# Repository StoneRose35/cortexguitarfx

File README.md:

# Introduction
The PiPicoFX is a simple multieffects unit for Guitar built around a Raspberry Pi Pico board. It is capable of serving as a standalone Amp-Simulator in conjuctions with a general-purpose PA system. 
## Audio Engine Specs
* 48 kHz sampling rate
* 0.6 ms Latency
* 16 bit fixed point accuracy
* Mono Input and output
## Controls
* 3 Parameters directly accessible via Knobs
* 128*64 Pixel monochrome display
* 1 Encoder, 2 Pushbuttons
* Analog Volume Control 
# Building
## Material needed
* Raspberry Pi Pico Board
* Audio Codec Board
* 128*64 Pixel OLED Display, compatible with SSD1306 driver
* Rotary Encoder (full quadrature)
* 5 10k Potentiometer
* 2 Pushbuttons
* 2 6.3 Mono Jacks 
* Enclosure
* Power Connector
## Audio-Codec Board
Generally an audio codec able to operate in 48 kHz I2S Master Mode is able to work with the raspberry pi pico. In fact at the beginning of the development even the internal ADC of the Pi Pico served as an input. The most straightforward and probably best-sounding way is to build the audio-codec pcb's using the [gerberfiles](schematics/guitarpreamp/audiocodecboard.zip) from your favorite small-batch manufacturer and then using the [bom](schematics/guitarpreamp/audiocodecboard_bom.csv) to order the parts from your preferred electronics distributor. Of course some SMD-soldering is required as well... 
### Schematic

## Software Installation
Download [pipicofx.uf2](pipicofx.uf2). Then connect the Raspberry Pi Pico while having the "boot" button depressed. Drag the file downloaded to the mass-storage device showing up, then you are done.

 ## Assembly
 Mount the UI Elements (Buttons, Encoder, Potentiometers, Jacks, Power connector) to the Enclosure the wire up the entire system using the sketch shown below

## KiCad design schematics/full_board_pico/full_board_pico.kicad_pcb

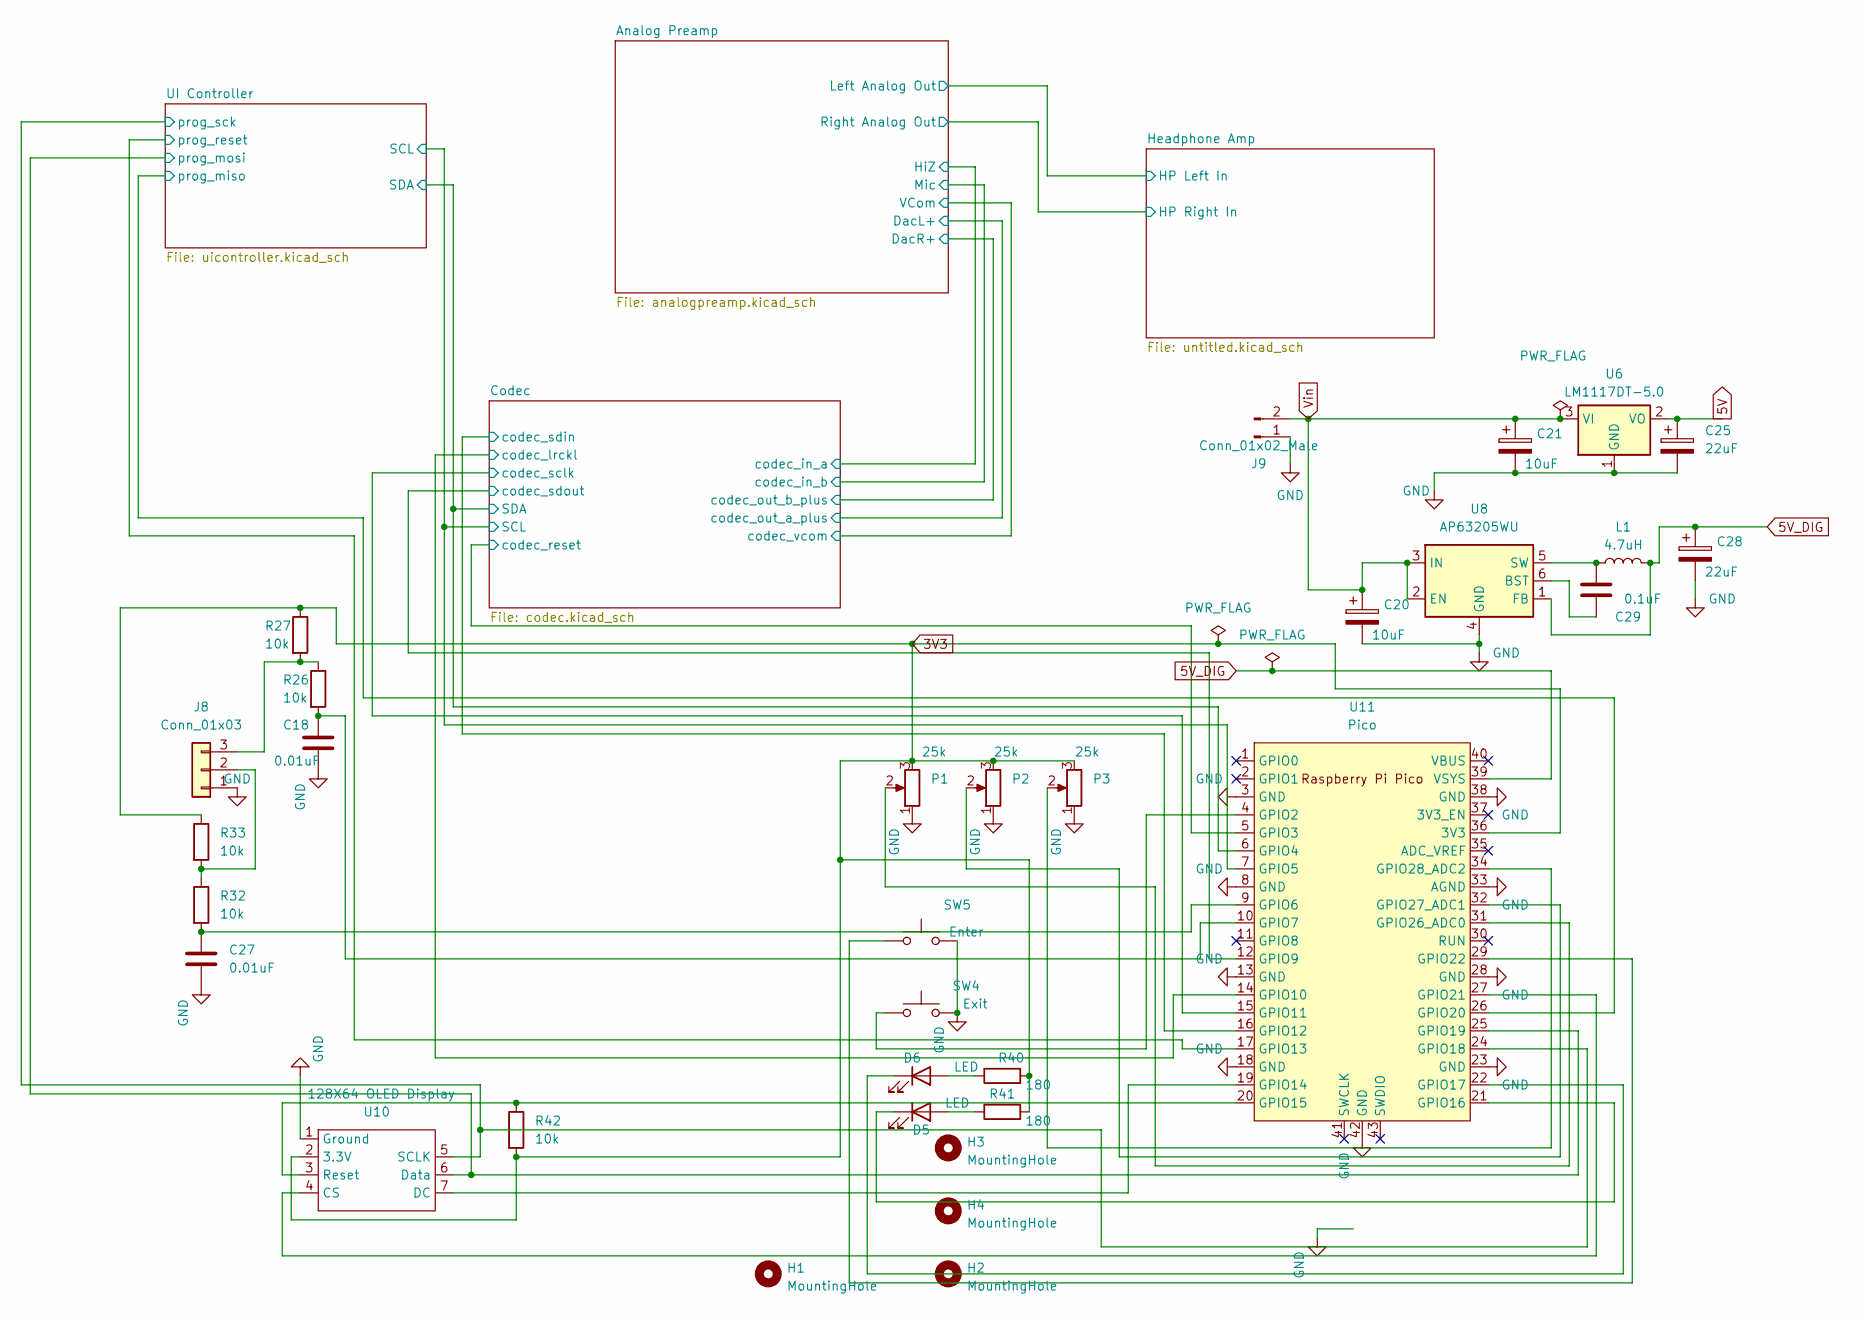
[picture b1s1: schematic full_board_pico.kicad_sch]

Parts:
C18, C27: 0.01uF; C_0805_2012Metric_Pad1.18x1.45mm_HandSolder
C20, C21: 10uF; CP_Elec_4x4.5
C25, C28: 22uF; CP_Elec_4x4.5
C29: 0.1uF; C_0805_2012Metric_Pad1.18x1.45mm_HandSolder
D5, D6: LED; PinHeader_1x02_P2.54mm_Vertical
H1, H2, H3, H4: MountingHole; MountingHole_4.3mm_M4
J8: Conn_01x03; PinHeader_1x03_P2.54mm_Vertical
J9: Conn_01x02_Male; PinHeader_1x02_P2.54mm_Vertical
L1: 4.7uH; L_Bourns_SRP7028A_7.3x6.6mm
P1, P2, P3: 25k; PinHeader_1x03_P2.54mm_Vertical
R26, R27, R32, R33, R42: 10k; R_0603_1608Metric_Pad0.98x0.95mm_HandSolder
R40, R41: 180; R_0603_1608Metric_Pad0.98x0.95mm_HandSolder
SW4: Exit; PinHeader_1x02_P2.54mm_Vertical
SW5: Enter; PinHeader_1x02_P2.54mm_Vertical
U6: LM1117DT-5.0; TO-252-2
U8: AP63205WU; TSOT-23-6
U10: 128X64 OLED Display; PinHeader_1x07_P2.54mm_Vertical
U11: Pico; RPi_Pico_SMD_TH

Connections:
5V_DIG: C28.1, L1.2, U8.1 (FB), U11.39 (VSYS)
/Codec/codec_lrckl: U11.14 (GPIO10); also elsewhere on the board
/Codec/codec_reset: U11.5 (GPIO3); also elsewhere on the board
/Codec/codec_sclk: U11.15 (GPIO11); also elsewhere on the board
/Codec/codec_sdin: U11.16 (GPIO12); also elsewhere on the board
/Codec/codec_sdout: U11.12 (GPIO9); also elsewhere on the board
/UI Controller/prog_miso: U11.26 (GPIO20); also elsewhere on the board
/UI Controller/prog_mosi: U10.6 (Data), U11.25 (GPIO19); also elsewhere on the board
/UI Controller/prog_reset: U11.17 (GPIO13); also elsewhere on the board
/UI Controller/prog_sck: U10.5 (SCLK), U11.24 (GPIO18); also elsewhere on the board
unnamed: D5.2 (A), R41.1
unnamed: D5.1 (K), U11.21 (GPIO16)
unnamed: D6.2 (A), R40.1
unnamed: D6.1 (K), U11.22 (GPIO17)
unnamed: J8.2, R32.1, R33.2
unnamed: J8.3, R26.1, R27.2
unnamed: C29.1, U8.6 (BST)
unnamed: C29.2, L1.1, U8.5 (SW)
unnamed: U10.4 (CS), U11.27 (GPIO21)
unnamed: U10.7 (DC), U11.19 (GPIO14)
unnamed: R42.1, U10.3 (Reset), U11.20 (GPIO15)
unnamed: SW4.1, U11.4 (GPIO2)
unnamed: C27.1, R32.2, U11.9 (GPIO6)
unnamed: C18.1, R26.2, U11.10 (GPIO7)
unnamed: SW5.1, U11.29 (GPIO22)
unnamed: P1.2, U11.31 (GPIO26_ADC0)
unnamed: P2.2, U11.32 (GPIO27_ADC1)
unnamed: P3.2, U11.34 (GPIO28_ADC2)
Vin: C20.1, C21.1, J9.2, U6.3 (VI), U8.2 (EN), U8.3 (IN)

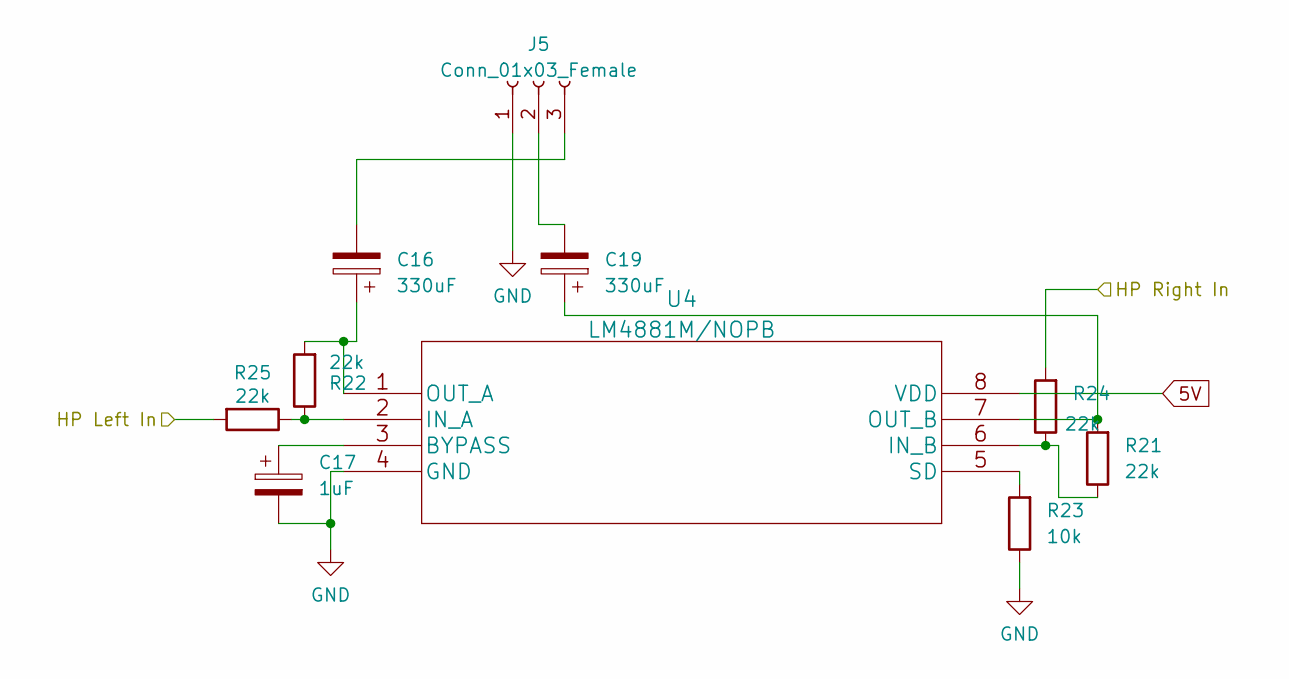
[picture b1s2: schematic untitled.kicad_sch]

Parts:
C16, C19: 330uF; CP_Elec_6.3x7.7
C17: 1uF; CP_Elec_4x4.5
J5: Conn_01x03_Female; PinHeader_1x03_P2.54mm_Vertical
R21, R22, R24, R25: 22k; R_0603_1608Metric_Pad0.98x0.95mm_HandSolder
R23: 10k; R_0603_1608Metric_Pad0.98x0.95mm_HandSolder
U4: LM4881M/NOPB; SOIC-8_3.9x4.9mm_P1.27mm

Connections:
unnamed: C19.2, J5.2
unnamed: C16.2, J5.3
unnamed: C17.1, U4.3 (BYPASS)
unnamed: R22.1, R25.1, U4.2 (IN_A)
unnamed: R21.1, R24.1, U4.6 (IN_B)
unnamed: C16.1, R22.2, U4.1 (OUT_A)
unnamed: C19.1, R21.2, U4.7 (OUT_B)
unnamed: R23.2, U4.5 (SD)

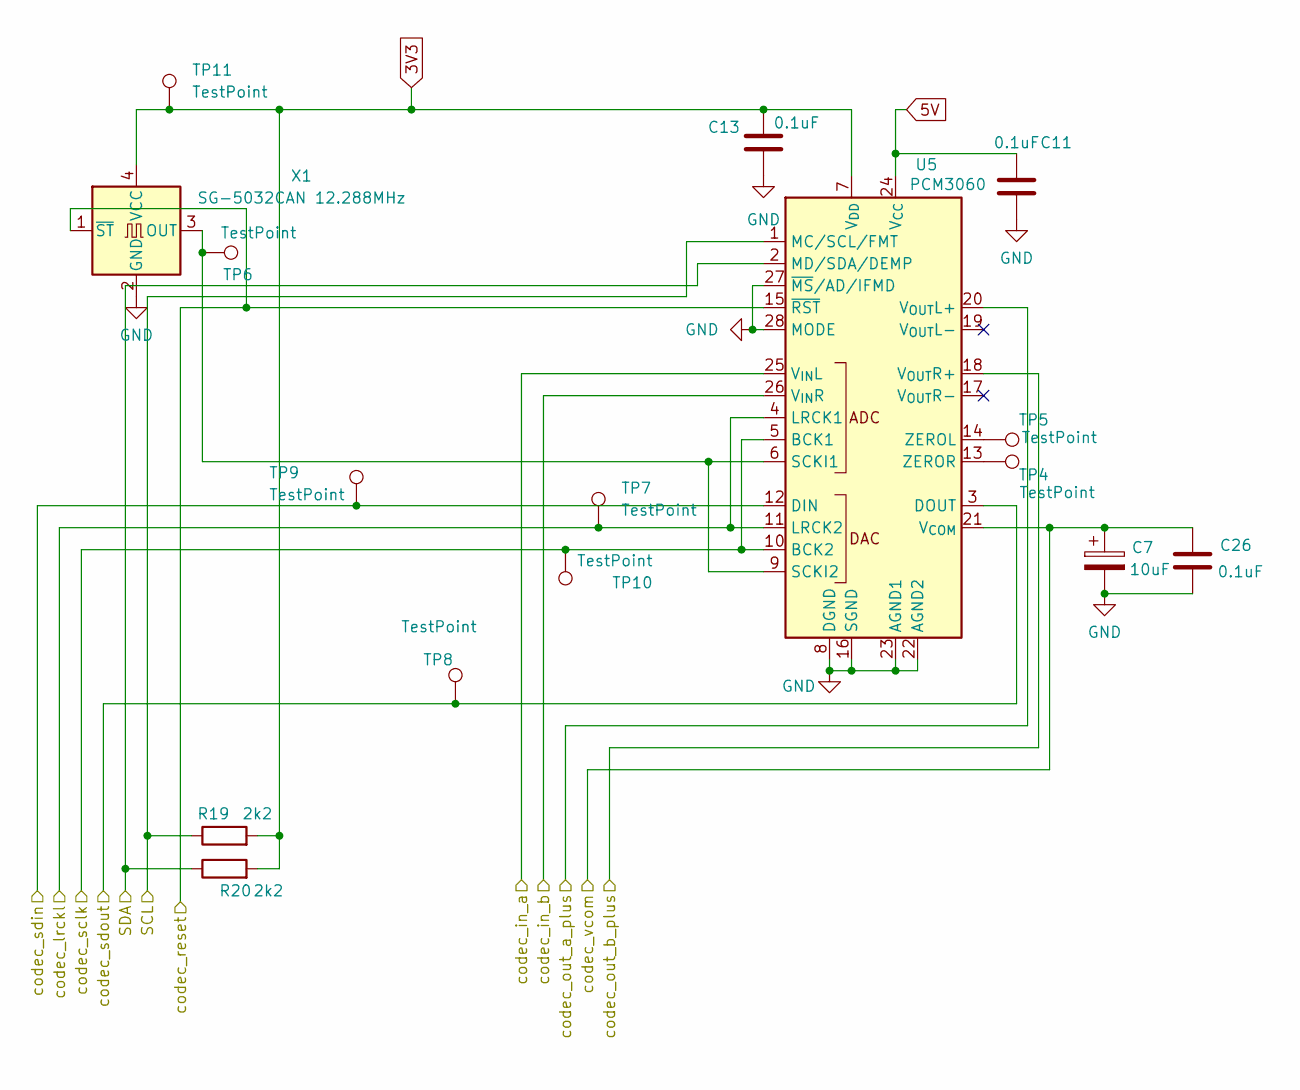
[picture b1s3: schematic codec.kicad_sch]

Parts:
C7: 10uF; CP_Elec_4x4.5
C11, C13, C26: 0.1uF; C_0805_2012Metric_Pad1.18x1.45mm_HandSolder
R19, R20: 2k2; R_0603_1608Metric_Pad0.98x0.95mm_HandSolder
TP4, TP5, TP6, TP7, TP8, TP9, TP10, TP11: TestPoint; TestPoint_Pad_D1.5mm
U5: PCM3060; TSSOP-28_4.4x9.7mm_P0.65mm
X1: SG-5032CAN 12.288MHz; Oscillator_SMD_SeikoEpson_SG8002CA-4Pin_7.0x5.0mm_HandSolde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

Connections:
/Analog Preamp/DacL+: U5.20 (V_{OUT}L+); also elsewhere on the board
/Analog Preamp/DacR+: U5.18 (V_{OUT}R+); also elsewhere on the board
/Analog Preamp/HiZ: U5.25 (V_{IN}L); also elsewhere on the board
/Analog Preamp/Mic: U5.26 (V_{IN}R); also elsewhere on the board
/Analog Preamp/VCom: C7.1, C26.1, U5.21 (V_{COM}); also elsewhere on the board
/Codec/codec_lrckl: TP7.1, U5.4 (LRCK1), U5.11 (LRCK2); also elsewhere on the board
/Codec/codec_reset: U5.15 (~RST), X1.1 (~ST); also elsewhere on the board
/Codec/codec_sclk: TP10.1, U5.5 (BCK1), U5.10 (BCK2); also elsewhere on the board
/Codec/codec_sdin: TP9.1, U5.12 (DIN); also elsewhere on the board
/Codec/codec_sdout: TP8.1, U5.3 (DOUT); also elsewhere on the board
unnamed: TP6.1, U5.6 (SCKI1), U5.9 (SCKI2), X1.3 (OUT)
unnamed: TP5.1, U5.14 (ZEROL)
unnamed: TP4.1, U5.13 (ZEROR)

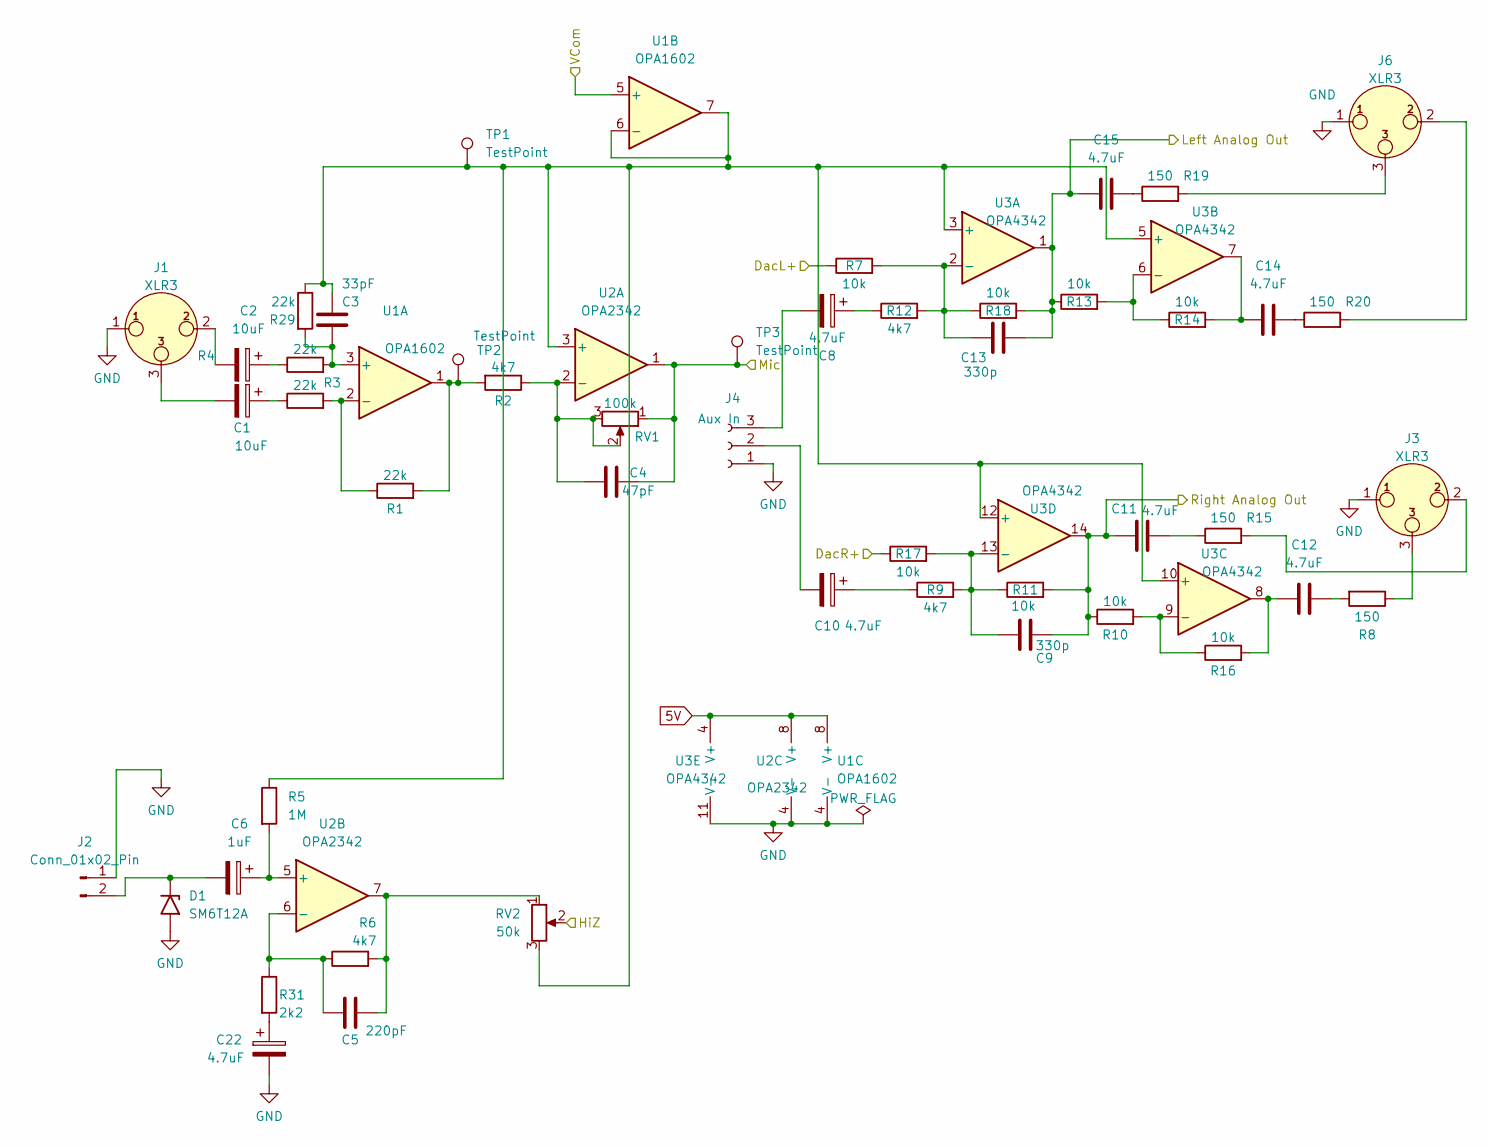
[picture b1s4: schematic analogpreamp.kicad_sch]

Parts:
C1, C2: 10uF; CP_Elec_4x4.5
C3: 33pF; C_0805_2012Metric_Pad1.18x1.45mm_HandSolder
C4: 47pF; C_0603_1608Metric_Pad1.08x0.95mm_HandSolder
C5: 220pF; C_0603_1608Metric_Pad1.08x0.95mm_HandSolder
C6: 1uF; CP_Elec_4x4.5
C8, C10, C22: 4.7uF; CP_Elec_4x4.5
C9, C13: 330p; C_0603_1608Metric_Pad1.08x0.95mm_HandSolder
C11, C12, C14, C15: 4.7uF; CP_Elec_5x5.4
D1: SM6T12A; D_SMB
J1, J3, J6: XLR3; PinHeader_1x03_P2.54mm_Vertical
J2: Conn_01x02_Pin; PinHeader_1x02_P2.54mm_Vertical
J4: Aux In; PinHeader_1x03_P2.54mm_Vertical
R1, R3, R4, R29: 22k; R_0603_1608Metric_Pad0.98x0.95mm_HandSolder
R2, R6, R9, R12: 4k7; R_0603_1608Metric_Pad0.98x0.95mm_HandSolder
R5: 1M; R_0603_1608Metric_Pad0.98x0.95mm_HandSolder
R7, R10, R11, R13, R14, R16, R17, R18: 10k; R_0603_1608Metric_Pad0.98x0.95mm_HandSolder
R8, R15, R19, R20: 150; R_0603_1608Metric_Pad0.98x0.95mm_HandSolder
R31: 2k2; R_0603_1608Metric_Pad0.98x0.95mm_HandSolder
RV1: 100k; PinHeader_1x03_P2.54mm_Vertical
RV2: 50k; PinHeader_1x03_P2.54mm_Vertical
TP1, TP2, TP3: TestPoint; TestPoint_Pad_D1.5mm
U1: OPA1602; SOIC-8_3.9x4.9mm_P1.27mm
U2: OPA2342; SOIC-8_3.9x4.9mm_P1.27mm
U3: OPA4342; SOIC-14_3.9x8.7mm_P1.27mm

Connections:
/Analog Preamp/DacL+: R7.1; also elsewhere on the board
/Analog Preamp/DacR+: R17.1; also elsewhere on the board
/Analog Preamp/HiZ: RV2.2; also elsewhere on the board
/Analog Preamp/Mic: C4.2, RV1.1, TP3.1, U2.1; also elsewhere on the board
/Analog Preamp/VCom: U1.5 (+); also elsewhere on the board
unnamed: C1.1, R3.1
unnamed: C1.2, J1.3
unnamed: C2.1, R4.1
unnamed: C2.2, J1.2
unnamed: C5.2, R6.2, RV2.1, U2.7
unnamed: C8.1, R12.1
unnamed: C10.1, R9.1
unnamed: C12.1, R16.2, U3.8
unnamed: C12.2, R8.2
unnamed: C14.1, R14.2, U3.7
unnamed: C22.1, R31.2
unnamed: C6.2, D1.1 (A1), J2.2
unnamed: J3.2, R15.2
unnamed: J3.3, R8.1
unnamed: C10.2, J4.2
unnamed: C8.2, J4.3
unnamed: R1.2, R2.2, TP2.1, U1.1
unnamed: C3.2, R4.2, R29.2, U1.3 (+)
unnamed: R1.1, R3.2, U1.2 (-)
unnamed: C3.1, R5.1, R29.1, RV2.3, TP1.1, U1.6 (-), U1.7, U2.3 (+), U3.3 (+), U3.5 (+), U3.10 (+), U3.12 (+)
unnamed: C4.1, R2.1, RV1.2, RV1.3, U2.2 (-)
unnamed: C6.1, R5.2, U2.5 (+)
unnamed: C5.1, R6.1, R31.1, U2.6 (-)
unnamed: R13.2, R14.1, U3.6 (-)
unnamed: R10.2, R16.1, U3.9 (-)
unnamed: C9.1, R9.2, R11.1, R17.2, U3.13 (-)

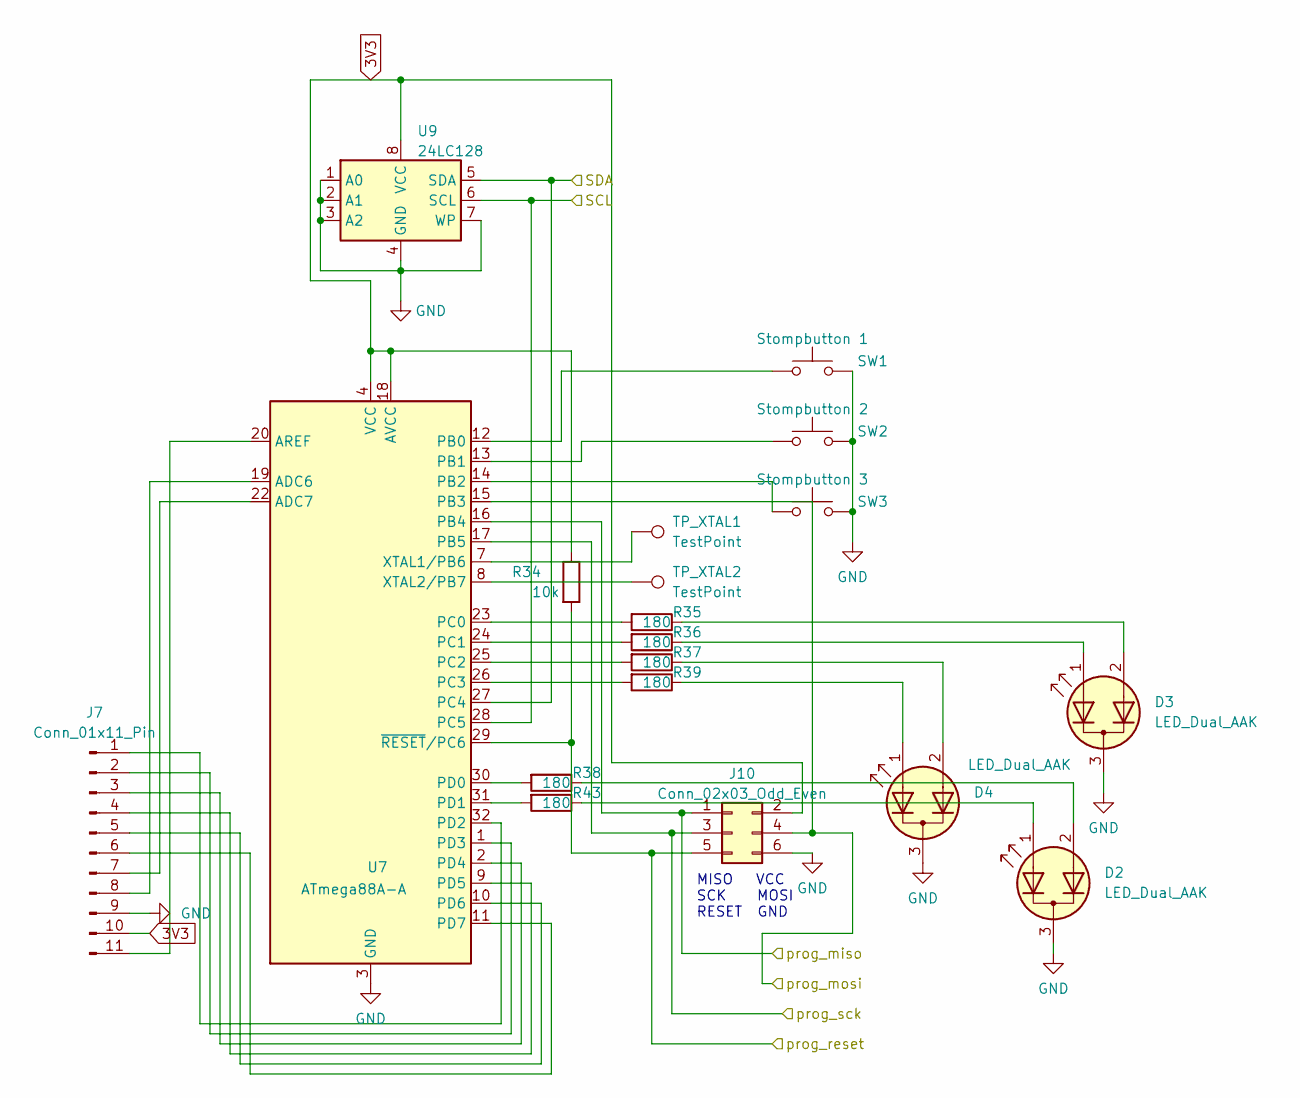
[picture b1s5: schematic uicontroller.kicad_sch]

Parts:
D2, D3, D4: LED_Dual_AAK; LED_D5.0mm-3
J7: Conn_01x11_Pin; PinHeader_1x11_P2.54mm_Vertical
J10: Conn_02x03_Odd_Even; PinHeader_2x03_P2.54mm_Vertical
R34: 10k; R_0603_1608Metric_Pad0.98x0.95mm_HandSolder
R35, R36, R37, R38, R39, R43: 180; R_0603_1608Metric_Pad0.98x0.95mm_HandSolder
SW1: Stompbutton 1; PinHeader_1x02_P2.54mm_Vertical
SW2: Stompbutton 2; PinHeader_1x02_P2.54mm_Vertical
SW3: Stompbutton 3; PinHeader_1x02_P2.54mm_Vertical
TP_XTAL1, TP_XTAL2: TestPoint; TestPoint_Pad_D1.5mm
U7: ATmega88A-A; TQFP-32_7x7mm_P0.8mm
U9: 24LC128; SOIC-8_3.9x4.9mm_P1.27mm

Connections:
/UI Controller/prog_miso: J10.1, U7.16 (PB4); also elsewhere on the board
/UI Controller/prog_mosi: J10.4, U7.15 (PB3); also elsewhere on the board
/UI Controller/prog_reset: J10.5, R34.2, U7.29 (~RESET/PC6); also elsewhere on the board
/UI Controller/prog_sck: J10.3, U7.17 (PB5); also elsewhere on the board
unnamed: D2.1 (A1), R43.1
unnamed: D2.2 (A2), R38.1
unnamed: D3.1 (A1), R36.1
unnamed: D3.2 (A2), R35.1
unnamed: D4.1 (A1), R39.1
unnamed: D4.2 (A2), R37.1
unnamed: J7.1, U7.32 (PD2)
unnamed: J7.2, U7.1 (PD3)
unnamed: J7.3, U7.2 (PD4)
unnamed: J7.4, U7.9 (PD5)
unnamed: J7.5, U7.10 (PD6)
unnamed: J7.6, U7.11 (PD7)
unnamed: J7.7, U7.22 (ADC7)
unnamed: J7.8, U7.19 (ADC6)
unnamed: J7.11, U7.20 (AREF)
unnamed: SW1.1, U7.12 (PB0)
unnamed: SW2.1, U7.13 (PB1)
unnamed: SW3.1, U7.14 (PB2)
unnamed: R35.2, U7.23 (PC0)
unnamed: R36.2, U7.24 (PC1)
unnamed: R37.2, U7.25 (PC2)
unnamed: R39.2, U7.26 (PC3)
unnamed: R38.2, U7.30 (PD0)
unnamed: R43.2, U7.31 (PD1)
unnamed: TP_XTAL1.1, U7.7 (XTAL1/PB6)
unnamed: TP_XTAL2.1, U7.8 (XTAL2/PB7)

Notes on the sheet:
MISO VCC SCK MOSI RESET GND

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
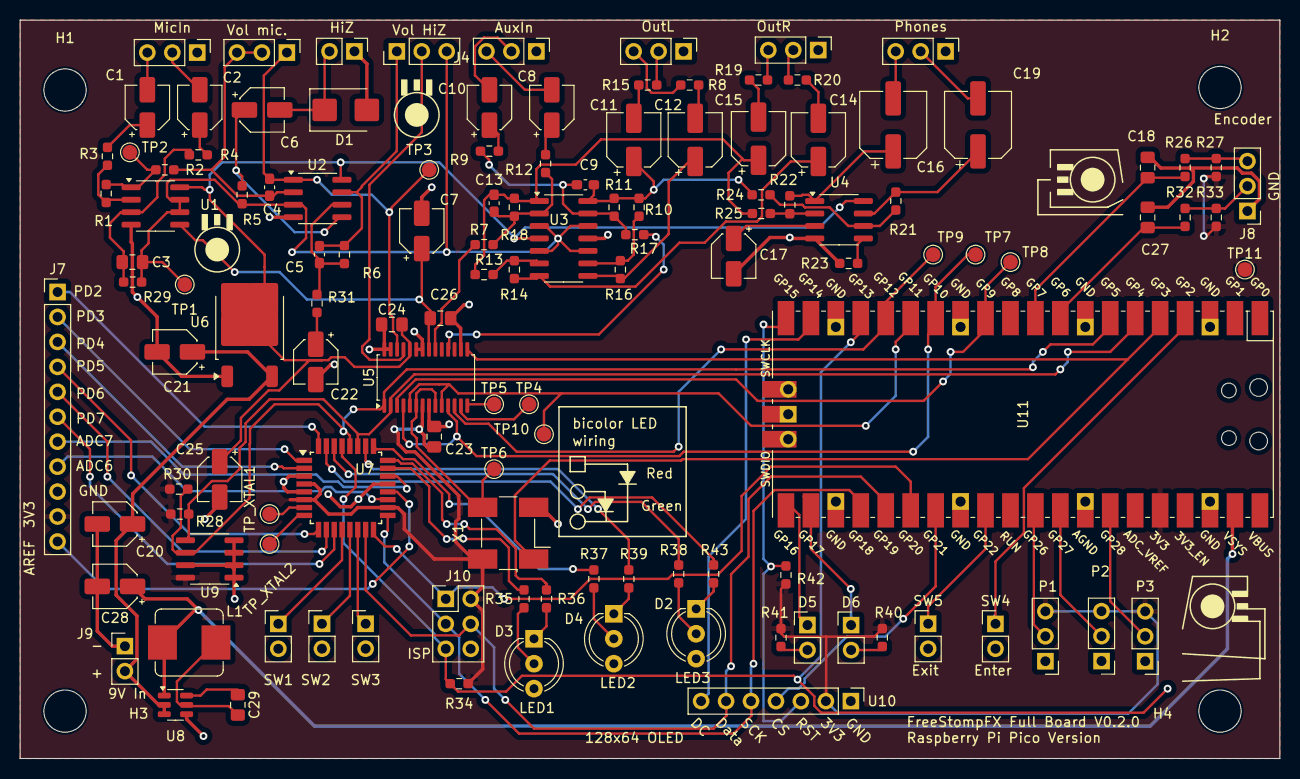
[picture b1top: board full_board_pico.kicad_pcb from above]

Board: 4 copper layers, 128.3 x 75.2 mm, 128 parts (0 on the bottom side), 110 nets.

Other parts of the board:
C23, C24: 0.1uF; C_0805_2012Metric_Pad1.18x1.45mm_HandSolder
R28, R30: 2k2; R_0603_1608Metric_Pad0.98x0.95mm_HandSolder

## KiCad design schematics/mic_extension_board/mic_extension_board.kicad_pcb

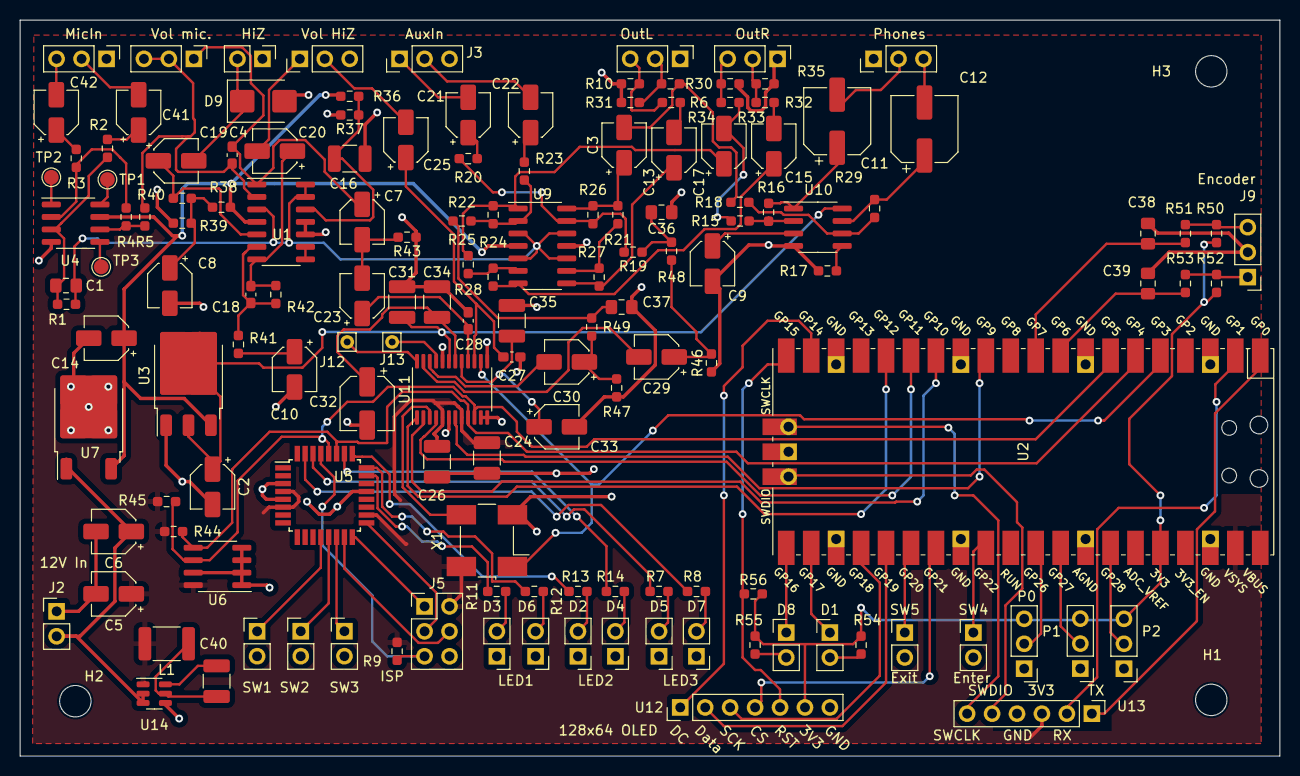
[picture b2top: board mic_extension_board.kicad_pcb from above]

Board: 4 copper layers, 128.3 x 74.9 mm, 149 parts (0 on the bottom side), 121 nets.

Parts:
C1: 33pF; C_0805_2012Metric_Pad1.18x1.45mm_HandSolder
C2, C7, C8, C9, C19, C20: 1uF; CP_Elec_4x4.5
C3, C6, C13, C15, C17, C23, C25, C33, C41, C42: 10uF; CP_Elec_4x4.5
C4: 47pF; C_0603_1608Metric_Pad1.08x0.95mm_HandSolder
C5, C14: 22uF; CP_Elec_4x4.5
C10, C21, C22: 4.7uF; CP_Elec_4x4.5
C11, C12: 330uF; CP_Elec_6.3x7.7
C16, C24, C26, C31, C34, C35, C40: 0.1uF; C_1210_3225Metric_Pad1.33x2.70mm_HandSolder
C18, C27, C28: 220pF; C_0603_1608Metric_Pad1.08x0.95mm_HandSolder
C29, C30: 3.3uF; CP_Elec_4x4.5
C32: 47uF; CP_Elec_5x5.4
C36, C37: 3.3nF; C_0805_2012Metric_Pad1.18x1.45mm_HandSolder
C38, C39: 0.01uF; C_0805_2012Metric_Pad1.18x1.45mm_HandSolder
D1, D2, D3, D4, D5, D6, D7, D8: LED; PinHeader_1x02_P2.54mm_Vertical
D9: SM6T12A; D_SMB
H1, H2, H3: MountingHole; MountingHole_3.2mm_M3
J1, J7, J8: XLR3; PinHeader_1x03_P2.54mm_Vertical
J2: Conn_01x02_Male; PinHeader_1x02_P2.54mm_Vertical
J3: Aux In; PinHeader_1x03_P2.54mm_Vertical
J4: Conn_01x02_Pin; PinHeader_1x02_P2.54mm_Vertical
J5: Conn_02x03_Odd_Even; PinHeader_2x03_P2.54mm_Vertical
J6: Conn_01x03_Female; PinHeader_1x03_P2.54mm_Vertical
J9: Conn_01x03; PinHeader_1x03_P2.54mm_Vertical
J12, J13: Conn_01x01_Female; Pin_D0.7mm_L6.5mm_W1.8mm_FlatFork
L1: 3.9uH; L_1812_4532Metric_Pad1.30x3.40mm_HandSolder
P0, P1, P2: 25k; PinHeader_1x03_P2.54mm_Vertical
R1, R2, R3, R4, R15, R16, R18, R29: 22k; R_0603_1608Metric_Pad0.98x0.95mm_HandSolder
R5, R20, R23, R42: 4k7; R_0603_1608Metric_Pad0.98x0.95mm_HandSolder
R6, R30, R32, R33: 150; R_0603_1608Metric_Pad0.98x0.95mm_HandSolder
R7, R8, R11, R12, R13, R14, R54, R55: 180; R_0603_1608Metric_Pad0.98x0.95mm_HandSolder
R9, R10, R17, R19, R21, R22, R24, R25, R26, R27, R28, R31, R34, R35, R46, R47, R50, R51, R52, R53, R56: 10k; R_0603_1608Metric_Pad0.98x0.95mm_HandSolder
R36, R37, R38, R39: 12k; R_0603_1608Metric_Pad0.98x0.95mm_HandSolder
R40: 1M; R_0603_1608Metric_Pad0.98x0.95mm_HandSolder
R41, R44, R45: 2k2; R_0603_1608Metric_Pad0.98x0.95mm_HandSolder
R43: 47k; R_0603_1608Metric_Pad0.98x0.95mm_HandSolder
R48, R49: 470; R_0603_1608Metric_Pad0.98x0.95mm_HandSolder
RV1: 100k; PinHeader_1x03_P2.54mm_Vertical
RV2: 10k; PinHeader_1x03_P2.54mm_Vertical
SW1: Stompbutton 1; PinHeader_1x02_P2.54mm_Vertical
SW2: Stompbutton 2; PinHeader_1x02_P2.54mm_Vertical
SW3: Stompbutton 3; PinHeader_1x02_P2.54mm_Vertical
SW4: Enter; PinHeader_1x02_P2.54mm_Vertical
SW5: Exit; PinHeader_1x02_P2.54mm_Vertical
TP1, TP2, TP3: TestPoint; TestPoint_Pad_D1.5mm
U1, U9: TL074; SOIC-14_3.9x8.7mm_P1.27mm
U2: Pico; RPi_Pico_SMD_TH
U3: LM1117DT-5.0; TO-252-3_TabPin2
U4: NE5534; SOIC-8_3.9x4.9mm_P1.27mm
U5: ATmega88A-A; TQFP-32_7x7mm_P0.8mm
U6: 24LC128; SOIC-8_3.9x4.9mm_P1.27mm
U7: MC78M05_TO252; TO-252-2
U10: LM4881M/NOPB; SOIC-8_3.9x4.9mm_P1.27mm
U11: CS4270-CZZ; TSSOP-24_4.4x7.8mm_P0.65mm
U12: 128X64 OLED Display; PinHeader_1x07_P2.54mm_Vertical
U13: Debug Port; PinHeader_1x06_P2.54mm_Vertical
U14: AP63203WU; TSOT-23-6
X1: SG-5032CAN; Oscillator_SMD_SeikoEpson_SG8002CA-4Pin_7.0x5.0mm_HandSolde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

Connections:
3V3: C5.1, C24.1, C26.1, J5.2, L1.2, R9.1, R44.2, R45.2, U2.39 (VSYS), U5.4 (VCC), U5.6 (VCC), U5.18 (AVCC), U6.8 (VCC), U11.5 (VD), U11.8 (VLC), U13.3 (Vsys), U14.1 (FB), X1.4 (VCC)
5V: C2.1, C31.2, U3.2 (VO), U10.8 (VDD), U11.19 (VA)
+9V: C14.1, R36.1, R38.1, U1.4 (V+), U3.3 (VI), U4.7 (V+), U7.3 (VO), U9.4 (V+)
/Analog Preamp/DacL: C37.2, R22.1, R49.2
/Analog Preamp/DacR: C36.2, R19.1, R48.2
/Analog Preamp/HiZ: C25.2, RV2.2
/Analog Preamp/Left Analog Out: C17.2, R15.2, R33.1
/Analog Preamp/Mic: C7.2, C23.2, R43.2
/Analog Preamp/Right Analog Out: C3.2, R18.2, R30.1
/Codec/SCL: R45.1, U2.7 (GPIO5), U5.28 (PC5), U6.6 (SCL), U11.10 (M0)
/Codec/SDA: R44.1, U2.6 (GPIO4), U5.27 (PC4), U6.5 (SDA), U11.9 (M1)
/Codec/codec_lrckl: U2.14 (GPIO10), U11.2 (LRCK)
/Codec/codec_reset: U2.5 (GPIO3), U11.14 (*RST), X1.1 (~ST)
/Codec/codec_sclk: U2.15 (GPIO11), U11.4 (SCLK)
/Codec/codec_sdin: U2.16 (GPIO12), U11.1 (SDIN)
/Codec/codec_sdout: U2.12 (GPIO9), U11.7 (SDOUT)
GND: C2.2, C5.2, C6.2, C8.2, C9.2, C10.2, C14.2, C16.2, C24.2, C26.2, C27.1, C28.1, C31.1, C32.2, C33.2, C34.1, C35.2, C36.1, C37.1, C38.2, C39.2, D2.1 (K), D3.1 (K), D4.1 (K), D5.1 (K), D6.1 (K), D7.1 (K), D9.2 (A2), J1.1, J2.1, J3.3, J4.1, J5.6, J6.1, J7.1, J8.1, J9.2, P0.1, P1.1, P2.1, R10.2, R17.1, R31.2, R34.2, R35.2, R37.2, R39.2, R43.1, R46.1, R47.1, RV2.3, SW1.2, SW2.2, SW3.2, SW4.2, SW5.2, U1.10 (+), U1.11 (V-), U2.3 (GND), U2.8 (GND), U2.13 (GND), U2.18 (GND), U2.23 (GND), U2.28 (GND), U2.33 (AGND), U2.38 (GND), U2.42 (GND), U3.1 (GND), U4.4 (V-), U5.3 (GND), U5.5 (GND), U5.21 (GND), U6.1 (A0), U6.2 (A1), U6.3 (A2), U6.4 (GND), U6.7 (WP), U7.2 (GND), U9.11 (V-), U10.4 (GND), U11.6 (DGND), U11.11 (I2S/*LJ), U11.12 (MDIV1), U11.13 (MDIV2), U11.20 (AGND), U12.7 (Ground), U13.4 (Ground), U14.4 (GND), X1.2 (GND)
unnamed: C3.1, R21.1, R26.2, U9.14
unnamed: C4.2, C7.1, RV1.1, U1.1
unnamed: C8.1, R38.2, R39.1, R40.1
unnamed: C10.1, R41.2
unnamed: C13.1, R27.2, U9.8
unnamed: C13.2, R6.2
unnamed: C15.1, R28.2, U9.7
unnamed: C15.2, R32.2
unnamed: C17.1, R24.2, R25.1, U9.1
unnamed: C18.2, C20.1, R42.2, U1.7
unnamed: C20.2, RV2.1
unnamed: C21.1, R20.1
unnamed: C22.1, R23.1
unnamed: C29.1, R46.2, R48.1
unnamed: C30.1, R47.2, R49.1
unnamed: C41.1, R2.1
unnamed: C41.2, J1.2
unnamed: C42.1, R3.1
unnamed: C42.2, J1.3
unnamed: D1.2 (A), R54.1
unnamed: D1.1 (K), U2.22 (GPIO17)
unnamed: D2.2 (A), R13.1
unnamed: D3.2 (A), R11.1
unnamed: D4.2 (A), R14.1
unnamed: D5.2 (A), R7.1
unnamed: D6.2 (A), R12.1
unnamed: D7.2 (A), R8.1
unnamed: D8.2 (A), R55.1
unnamed: D8.1 (K), U2.21 (GPIO16)
unnamed: C19.2, D9.1 (A1), J4.2
unnamed: C21.2, J3.1
unnamed: C22.2, J3.2
unnamed: J5.1, U5.16 (PB4)
unnamed: J5.3, U5.17 (PB5)
unnamed: J5.4, U5.15 (PB3)
unnamed: J5.5, R9.2, U5.29 (~RESET/PC6)
unnamed: C11.2, J6.2
unnamed: C12.2, J6.3
unnamed: J7.2, R30.2, R31.1
unnamed: J7.3, R6.1, R10.1
unnamed: J8.2, R32.1, R35.1
unnamed: J8.3, R33.2, R34.1
unnamed: J9.1, R52.2, R53.1
unnamed: J9.3, R50.2, R51.1
unnamed: J12.1, U11.24 (*MUTEB)
unnamed: J13.1, U11.21 (*MUTEA)
unnamed: R4.2, R5.2, U4.6
unnamed: C4.1, R5.1, RV1.2, RV1.3, U1.2 (-)
unnamed: C19.1, R40.2, U1.5 (+)
unnamed: C18.1, R41.1, R42.1, U1.6 (-)
unnamed: U1.8, U1.9 (-)
unnamed: C16.1, R36.2, R37.1, U1.12 (+)
unnamed: C39.1, R53.2, U2.9 (GPIO6)
unnamed: C38.1, R51.2, U2.10 (GPIO7)
unnamed: SW5.1, U2.26 (GPIO20)
unnamed: SW4.1, U2.29 (GPIO22)
unnamed: P0.2, U2.31 (GPIO26_ADC0)
unnamed: P1.2, U2.32 (GPIO27_ADC1)
unnamed: P2.2, U2.34 (GPIO28_ADC2)
unnamed: C1.2, R1.2, R2.2, U4.3 (+)
unnamed: R3.2, R4.1, U4.2 (-)
unnamed: TP2.1, U4.1 (BAL)
unnamed: TP3.1, U4.5 (COMP)
unnamed: TP1.1, U4.8 (C/B)
unnamed: SW1.1, U5.12 (PB0)
unnamed: SW2.1, U5.13 (PB1)
unnamed: SW3.1, U5.14 (PB2)
unnamed: R11.2, U5.23 (PC0)
unnamed: R12.2, U5.24 (PC1)
unnamed: R13.2, U5.25 (PC2)
unnamed: R14.2, U5.26 (PC3)
unnamed: R7.2, U5.30 (PD0)
unnamed: R8.2, U5.31 (PD1)
unnamed: R22.2, R23.2, R24.1, U9.2 (-)
unnamed: R25.2, R28.1, U9.6 (-)
unnamed: R21.2, R27.1, U9.9 (-)
unnamed: R19.2, R20.2, R26.1, U9.13 (-)
unnamed: C9.1, U10.3 (BYPASS)
unnamed: R15.1, R16.1, U10.2 (IN_A)
unnamed: R18.1, R29.1, U10.6 (IN_B)
unnamed: C11.1, R16.2, U10.1 (OUT_A)
unnamed: C12.1, R29.2, U10.7 (OUT_B)
unnamed: R17.2, U10.5 (SD)
unnamed: C25.1, C27.2, U11.15 (AINA)
unnamed: C23.1, C28.2, U11.16 (AINB)
unnamed: C30.2, U11.22 (AOUTA)
unnamed: C29.2, U11.23 (AOUTB)
unnamed: C32.1, C34.2, U11.18 (FILT+)
unnamed: U11.3 (MCLK), X1.3 (OUT)
unnamed: C33.1, C35.1, U11.17 (VQ)
unnamed: P0.3, P1.3, P2.3, R50.1, R52.1, R54.2, R55.2, R56.2, U2.36 (3V3), U12.6 (3.3V)
unnamed: U2.27 (GPIO21), U12.4 (CS)
unnamed: U2.19 (GPIO14), U12.1 (DC)
unnamed: U2.25 (GPIO19), U12.2 (Data)
unnamed: R56.1, U2.20 (GPIO15), U12.5 (Reset)
unnamed: U2.24 (GPIO18), U12.3 (SCLK)
unnamed: U2.41 (SWCLK), U13.6 (SWCLK)
unnamed: U2.43 (SWDIO), U13.5 (SWDIO)
unnamed: U2.2 (GPIO1), U13.2 (UartRX)
unnamed: U2.1 (GPIO0), U13.1 (UartTX)
unnamed: C40.1, U14.6 (BST)
unnamed: C40.2, L1.1, U14.5 (SW)
VGND: C1.1, R1.1, U1.3 (+), U1.13 (-), U1.14, U9.3 (+), U9.5 (+), U9.10 (+), U9.12 (+)
Vin: C6.1, J2.2, U7.1 (VI), U14.2 (EN), U14.3 (IN)
